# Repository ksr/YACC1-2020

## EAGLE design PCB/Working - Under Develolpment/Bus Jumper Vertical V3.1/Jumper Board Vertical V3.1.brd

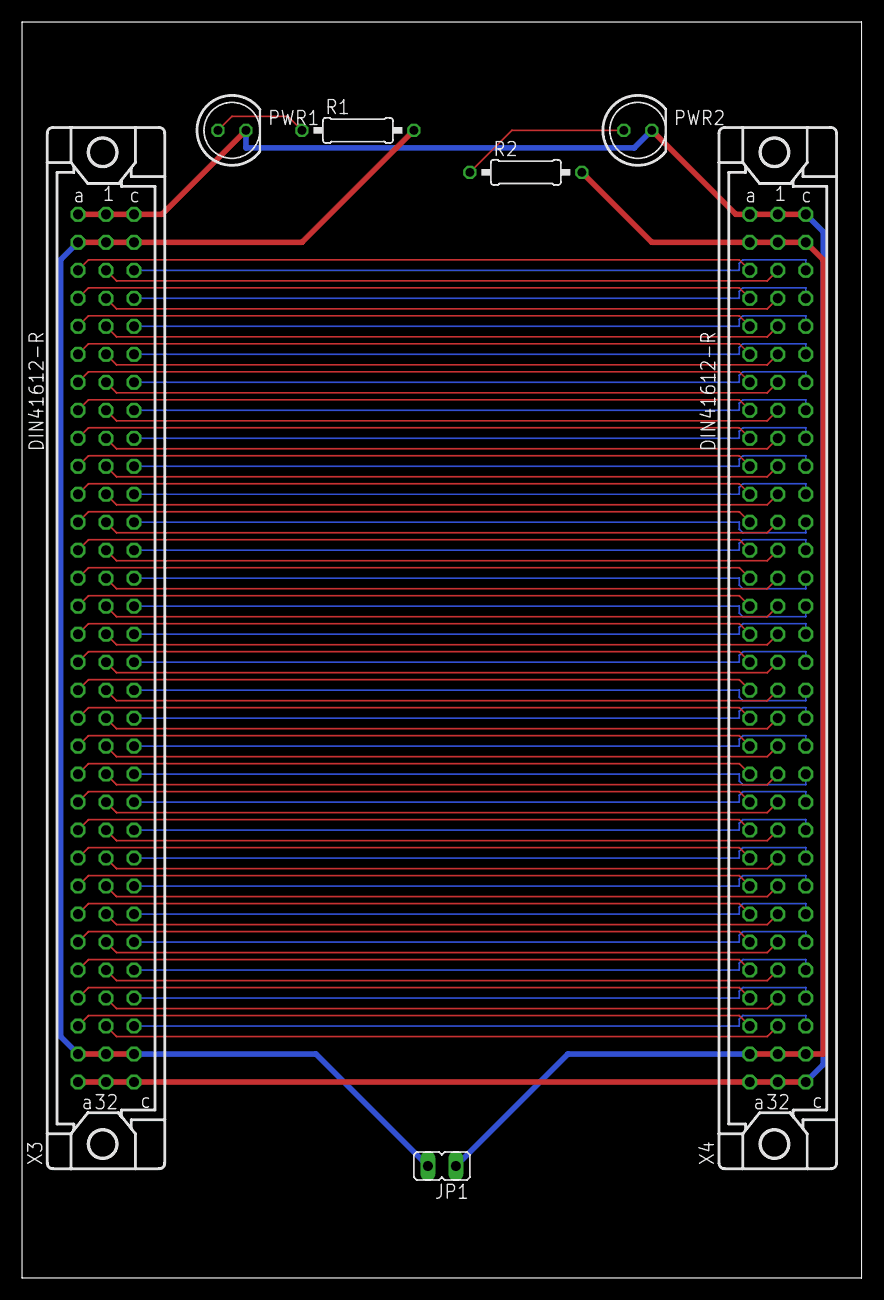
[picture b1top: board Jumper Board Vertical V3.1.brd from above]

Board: 2 copper layers, 76.2 x 114.0 mm, 7 parts (0 on the bottom side), 89 nets.

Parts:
JP1: JP1
PWR1, PWR2: LED5MM
R1, R2: 330; 0207/10
X3, X4: MABC96R

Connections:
GND: PWR1.K, PWR2.K, X3.A1, X3.A32, X3.B1, X3.B32, X3.C1, X3.C32, X4.A1, X4.A32, X4.B1, X4.B32, X4.C1, X4.C32
unnamed: X3.A3, X4.A3
unnamed: X3.A4, X4.A4
unnamed: X3.A5, X4.A5
unnamed: X3.A6, X4.A6
unnamed: X3.A7, X4.A7
unnamed: X3.A8, X4.A8
unnamed: X3.A9, X4.A9
unnamed: X3.A10, X4.A10
unnamed: X3.A11, X4.A11
unnamed: X3.A12, X4.A12
unnamed: X3.A13, X4.A13
unnamed: X3.A14, X4.A14
unnamed: X3.A15, X4.A15
unnamed: X3.A16, X4.A16
unnamed: X3.A17, X4.A17
unnamed: X3.A18, X4.A18
unnamed: X3.A19, X4.A19
unnamed: X3.A20, X4.A20
unnamed: X3.A21, X4.A21
unnamed: X3.A22, X4.A22
unnamed: X3.A23, X4.A23
unnamed: X3.A24, X4.A24
unnamed: X3.A25, X4.A25
unnamed: X3.A26, X4.A26
unnamed: X3.A27, X4.A27
unnamed: X3.A28, X4.A28
unnamed: X3.A29, X4.A29
unnamed: X3.A30, X4.A30
unnamed: PWR1.A, R1.1
unnamed: PWR2.A, R2.1
unnamed: X3.B3, X4.B3
unnamed: X3.B4, X4.B4
unnamed: X3.B5, X4.B5
unnamed: X3.B6, X4.B6
unnamed: X3.B7, X4.B7
unnamed: X3.B8, X4.B8
unnamed: X3.B9, X4.B9
unnamed: X3.B10, X4.B10
unnamed: X3.B11, X4.B11
unnamed: X3.B12, X4.B12
unnamed: X3.B13, X4.B13
unnamed: X3.B14, X4.B14
unnamed: X3.B15, X4.B15
unnamed: X3.B16, X4.B16
unnamed: X3.B17, X4.B17
unnamed: X3.B18, X4.B18
unnamed: X3.B19, X4.B19
unnamed: X3.B20, X4.B20
unnamed: X3.B21, X4.B21
unnamed: X3.B22, X4.B22
unnamed: X3.B23, X4.B23
unnamed: X3.B24, X4.B24
unnamed: X3.B25, X4.B25
unnamed: X3.B26, X4.B26
unnamed: X3.B27, X4.B27
unnamed: X3.B28, X4.B28
unnamed: X3.B29, X4.B29
unnamed: X3.B30, X4.B30
unnamed: X3.C3, X4.C3
unnamed: X3.C4, X4.C4
unnamed: X3.C5, X4.C5
unnamed: X3.C6, X4.C6
unnamed: X3.C7, X4.C7
unnamed: X3.C8, X4.C8
unnamed: X3.C9, X4.C9
unnamed: X3.C10, X4.C10
unnamed: X3.C11, X4.C11
unnamed: X3.C12, X4.C12
unnamed: X3.C13, X4.C13
unnamed: X3.C14, X4.C14
unnamed: X3.C15, X4.C15
unnamed: X3.C16, X4.C16
unnamed: X3.C17, X4.C17
unnamed: X3.C18, X4.C18
unnamed: X3.C19, X4.C19
unnamed: X3.C20, X4.C20
unnamed: X3.C21, X4.C21
unnamed: X3.C22, X4.C22
unnamed: X3.C23, X4.C23
unnamed: X3.C24, X4.C24
unnamed: X3.C25, X4.C25
unnamed: X3.C26, X4.C26
unnamed: X3.C27, X4.C27
unnamed: X3.C28, X4.C28
unnamed: X3.C29, X4.C29
unnamed: X3.C30, X4.C30
V1: JP1.2, R1.2, X3.A2, X3.A31, X3.B2, X3.B31, X3.C2, X3.C31
V2: JP1.1, R2.2, X4.A2, X4.A31, X4.B2, X4.B31, X4.C2, X4.C31

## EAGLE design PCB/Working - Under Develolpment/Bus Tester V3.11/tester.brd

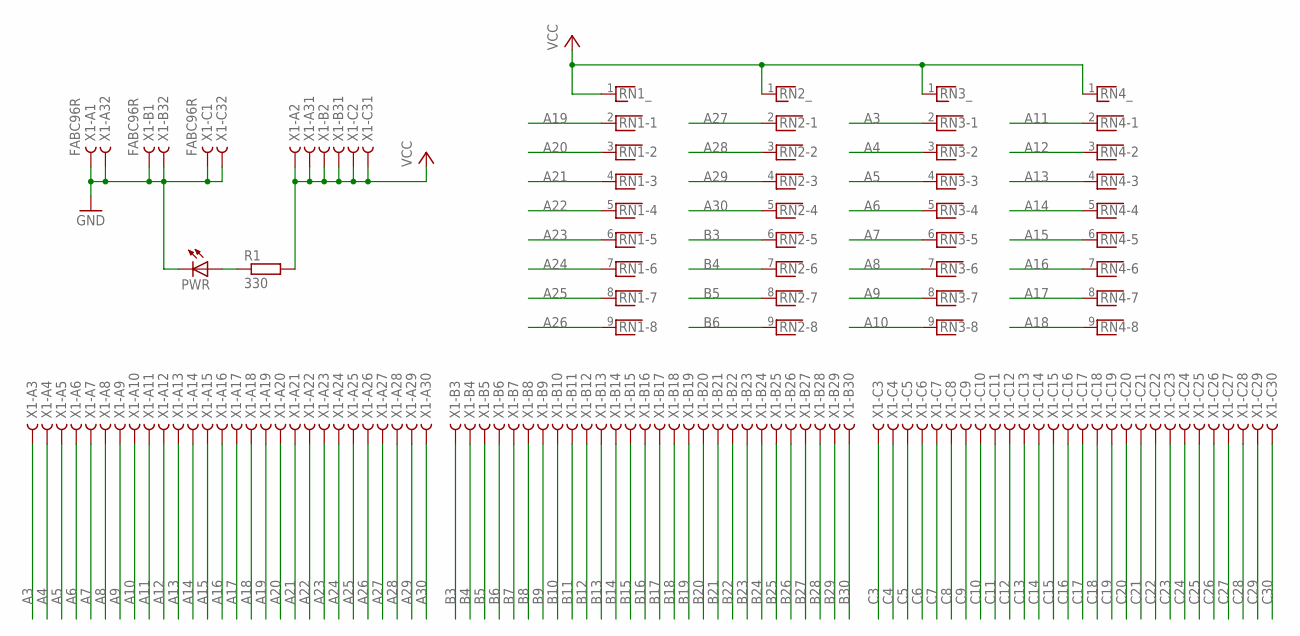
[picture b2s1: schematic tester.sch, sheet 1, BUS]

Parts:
PWR: LED5MM
R1: 330; 0207/10
RN1, RN2, RN3, RN4: RNX8; RN-9
X1: FABC96R

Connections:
A3: RN3.2, X1.A3; also elsewhere on the board
A4: RN3.3, X1.A4; also elsewhere on the board
A5: RN3.4, X1.A5; also elsewhere on the board
A6: RN3.5, X1.A6; also elsewhere on the board
A7: RN3.6, X1.A7; also elsewhere on the board
A8: RN3.7, X1.A8; also elsewhere on the board
A9: RN3.8, X1.A9; also elsewhere on the board
A10: RN3.9, X1.A10; also elsewhere on the board
A11: RN4.2, X1.A11; also elsewhere on the board
A12: RN4.3, X1.A12; also elsewhere on the board
A13: RN4.4, X1.A13; also elsewhere on the board
A14: RN4.5, X1.A14; also elsewhere on the board
A15: RN4.6, X1.A15; also elsewhere on the board
A16: RN4.7, X1.A16; also elsewhere on the board
A17: RN4.8, X1.A17; also elsewhere on the board
A18: RN4.9, X1.A18; also elsewhere on the board
A19: RN1.2, X1.A19; also elsewhere on the board
A20: RN1.3, X1.A20; also elsewhere on the board
A21: RN1.4, X1.A21; also elsewhere on the board
A22: RN1.5, X1.A22; also elsewhere on the board
A23: RN1.6, X1.A23; also elsewhere on the board
A24: RN1.7, X1.A24; also elsewhere on the board
A25: RN1.8, X1.A25; also elsewhere on the board
A26: RN1.9, X1.A26; also elsewhere on the board
A27: RN2.2, X1.A27; also elsewhere on the board
A28: RN2.3, X1.A28; also elsewhere on the board
A29: RN2.4, X1.A29; also elsewhere on the board
A30: RN2.5, X1.A30; also elsewhere on the board
B3: RN2.6, X1.B3; also elsewhere on the board
B4: RN2.7, X1.B4; also elsewhere on the board
B5: RN2.8, X1.B5; also elsewhere on the board
B6: RN2.9, X1.B6; also elsewhere on the board
B7: X1.B7; also elsewhere on the board
B8: X1.B8; also elsewhere on the board
B9: X1.B9; also elsewhere on the board
B10: X1.B10; also elsewhere on the board
B11: X1.B11; also elsewhere on the board
B12: X1.B12; also elsewhere on the board
B13: X1.B13; also elsewhere on the board
B14: X1.B14; also elsewhere on the board
B15: X1.B15; also elsewhere on the board
B16: X1.B16; also elsewhere on the board
B17: X1.B17; also elsewhere on the board
B18: X1.B18; also elsewhere on the board
B19: X1.B19; also elsewhere on the board
B20: X1.B20; also elsewhere on the board
B21: X1.B21; also elsewhere on the board
B22: X1.B22; also elsewhere on the board
B23: X1.B23; also elsewhere on the board
B24: X1.B24; also elsewhere on the board
B25: X1.B25; also elsewhere on the board
B26: X1.B26; also elsewhere on the board
B27: X1.B27; also elsewhere on the board
B28: X1.B28; also elsewhere on the board
B29: X1.B29; also elsewhere on the board
B30: X1.B30; also elsewhere on the board
C3: X1.C3; also elsewhere on the board
C4: X1.C4; also elsewhere on the board
C5: X1.C5; also elsewhere on the board
C6: X1.C6; also elsewhere on the board
C7: X1.C7; also elsewhere on the board
C8: X1.C8; also elsewhere on the board
C9: X1.C9; also elsewhere on the board
C10: X1.C10; also elsewhere on the board
C11: X1.C11; also elsewhere on the board
C12: X1.C12; also elsewhere on the board
C13: X1.C13; also elsewhere on the board
C14: X1.C14; also elsewhere on the board
C15: X1.C15; also elsewhere on the board
C16: X1.C16; also elsewhere on the board
C17: X1.C17; also elsewhere on the board
C18: X1.C18; also elsewhere on the board
C19: X1.C19; also elsewhere on the board
C20: X1.C20; also elsewhere on the board
C21: X1.C21; also elsewhere on the board
C22: X1.C22; also elsewhere on the board
C23: X1.C23; also elsewhere on the board
C24: X1.C24; also elsewhere on the board
C25: X1.C25; also elsewhere on the board
C26: X1.C26; also elsewhere on the board
C27: X1.C27; also elsewhere on the board
C28: X1.C28; also elsewhere on the board
C29: X1.C29; also elsewhere on the board
C30: X1.C30; also elsewhere on the board
GND: PWR.K (C), X1.A1, X1.A32, X1.B1, X1.B32, X1.C1, X1.C32; also elsewhere on the board
unnamed: PWR.A, R1.1
VCC: R1.2, RN1.1, RN2.1, RN3.1, RN4.1, X1.A2, X1.A31, X1.B2, X1.B31, X1.C2, X1.C31; also elsewhere on the board

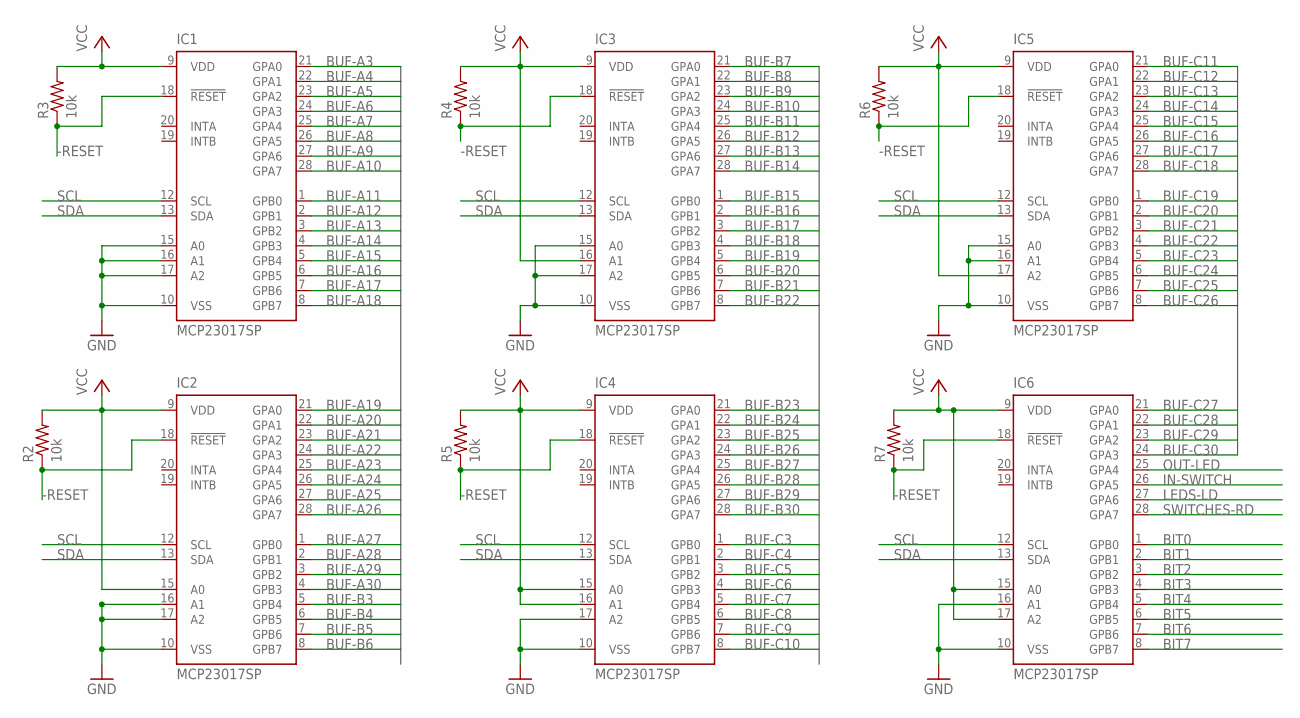
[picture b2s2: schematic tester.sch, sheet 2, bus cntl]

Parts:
IC1, IC2, IC3, IC4, IC5, IC6: MCP23017SP; DIL28-3
R2, R3, R4, R5, R6, R7: 10k; 0207/10

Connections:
-RESET: IC1.18 (!RESET), IC2.18 (!RESET), IC3.18 (!RESET), IC4.18 (!RESET), IC5.18 (!RESET), IC6.18 (!RESET), R2.1, R3.1, R4.1, R5.1, R6.1, R7.1; also elsewhere on the board
BIT0: IC6.1 (GPB0); also elsewhere on the board
BIT1: IC6.2 (GPB1); also elsewhere on the board
BIT2: IC6.3 (GPB2); also elsewhere on the board
BIT3: IC6.4 (GPB3); also elsewhere on the board
BIT4: IC6.5 (GPB4); also elsewhere on the board
BIT5: IC6.6 (GPB5); also elsewhere on the board
BIT6: IC6.7 (GPB6); also elsewhere on the board
BIT7: IC6.8 (GPB7); also elsewhere on the board
BUF-A3: IC1.21 (GPA0); also elsewhere on the board
BUF-A4: IC1.22 (GPA1); also elsewhere on the board
BUF-A5: IC1.23 (GPA2); also elsewhere on the board
BUF-A6: IC1.24 (GPA3); also elsewhere on the board
BUF-A7: IC1.25 (GPA4); also elsewhere on the board
BUF-A8: IC1.26 (GPA5); also elsewhere on the board
BUF-A9: IC1.27 (GPA6); also elsewhere on the board
BUF-A10: IC1.28 (GPA7); also elsewhere on the board
BUF-A11: IC1.1 (GPB0); also elsewhere on the board
BUF-A12: IC1.2 (GPB1); also elsewhere on the board
BUF-A13: IC1.3 (GPB2); also elsewhere on the board
BUF-A14: IC1.4 (GPB3); also elsewhere on the board
BUF-A15: IC1.5 (GPB4); also elsewhere on the board
BUF-A16: IC1.6 (GPB5); also elsewhere on the board
BUF-A17: IC1.7 (GPB6); also elsewhere on the board
BUF-A18: IC1.8 (GPB7); also elsewhere on the board
BUF-A19: IC2.21 (GPA0); also elsewhere on the board
BUF-A20: IC2.22 (GPA1); also elsewhere on the board
BUF-A21: IC2.23 (GPA2); also elsewhere on the board
BUF-A22: IC2.24 (GPA3); also elsewhere on the board
BUF-A23: IC2.25 (GPA4); also elsewhere on the board
BUF-A24: IC2.26 (GPA5); also elsewhere on the board
BUF-A25: IC2.27 (GPA6); also elsewhere on the board
BUF-A26: IC2.28 (GPA7); also elsewhere on the board
BUF-A27: IC2.1 (GPB0); also elsewhere on the board
BUF-A28: IC2.2 (GPB1); also elsewhere on the board
BUF-A29: IC2.3 (GPB2); also elsewhere on the board
BUF-A30: IC2.4 (GPB3); also elsewhere on the board
BUF-B3: IC2.5 (GPB4); also elsewhere on the board
BUF-B4: IC2.6 (GPB5); also elsewhere on the board
BUF-B5: IC2.7 (GPB6); also elsewhere on the board
BUF-B6: IC2.8 (GPB7); also elsewhere on the board
BUF-B7: IC3.21 (GPA0); also elsewhere on the board
BUF-B8: IC3.22 (GPA1); also elsewhere on the board
BUF-B9: IC3.23 (GPA2); also elsewhere on the board
BUF-B10: IC3.24 (GPA3); also elsewhere on the board
BUF-B11: IC3.25 (GPA4); also elsewhere on the board
BUF-B12: IC3.26 (GPA5); also elsewhere on the board
BUF-B13: IC3.27 (GPA6); also elsewhere on the board
BUF-B14: IC3.28 (GPA7); also elsewhere on the board
BUF-B15: IC3.1 (GPB0); also elsewhere on the board
BUF-B16: IC3.2 (GPB1); also elsewhere on the board
BUF-B17: IC3.3 (GPB2); also elsewhere on the board
BUF-B18: IC3.4 (GPB3); also elsewhere on the board
BUF-B19: IC3.5 (GPB4); also elsewhere on the board
BUF-B20: IC3.6 (GPB5); also elsewhere on the board
BUF-B21: IC3.7 (GPB6); also elsewhere on the board
BUF-B22: IC3.8 (GPB7); also elsewhere on the board
BUF-B23: IC4.21 (GPA0); also elsewhere on the board
BUF-B24: IC4.22 (GPA1); also elsewhere on the board
BUF-B25: IC4.23 (GPA2); also elsewhere on the board
BUF-B26: IC4.24 (GPA3); also elsewhere on the board
BUF-B27: IC4.25 (GPA4); also elsewhere on the board
BUF-B28: IC4.26 (GPA5); also elsewhere on the board
BUF-B29: IC4.27 (GPA6); also elsewhere on the board
BUF-B30: IC4.28 (GPA7); also elsewhere on the board
BUF-C3: IC4.1 (GPB0); also elsewhere on the board
BUF-C4: IC4.2 (GPB1); also elsewhere on the board
BUF-C5: IC4.3 (GPB2); also elsewhere on the board
BUF-C6: IC4.4 (GPB3); also elsewhere on the board
BUF-C7: IC4.5 (GPB4); also elsewhere on the board
BUF-C8: IC4.6 (GPB5); also elsewhere on the board
BUF-C9: IC4.7 (GPB6); also elsewhere on the board
BUF-C10: IC4.8 (GPB7); also elsewhere on the board
BUF-C11: IC5.21 (GPA0); also elsewhere on the board
BUF-C12: IC5.22 (GPA1); also elsewhere on the board
BUF-C13: IC5.23 (GPA2); also elsewhere on the board
BUF-C14: IC5.24 (GPA3); also elsewhere on the board
BUF-C15: IC5.25 (GPA4); also elsewhere on the board
BUF-C16: IC5.26 (GPA5); also elsewhere on the board
BUF-C17: IC5.27 (GPA6); also elsewhere on the board
BUF-C18: IC5.28 (GPA7); also elsewhere on the board
BUF-C19: IC5.1 (GPB0); also elsewhere on the board
BUF-C20: IC5.2 (GPB1); also elsewhere on the board
BUF-C21: IC5.3 (GPB2); also elsewhere on the board
BUF-C22: IC5.4 (GPB3); also elsewhere on the board
BUF-C23: IC5.5 (GPB4); also elsewhere on the board
BUF-C24: IC5.6 (GPB5); also elsewhere on the board
BUF-C25: IC5.7 (GPB6); also elsewhere on the board
BUF-C26: IC5.8 (GPB7); also elsewhere on the board
BUF-C27: IC6.21 (GPA0); also elsewhere on the board
BUF-C28: IC6.22 (GPA1); also elsewhere on the board
BUF-C29: IC6.23 (GPA2); also elsewhere on the board
BUF-C30: IC6.24 (GPA3); also elsewhere on the board
GND: IC1.10 (VSS), IC1.15 (A0), IC1.16 (A1), IC1.17 (A2), IC2.10 (VSS), IC2.16 (A1), IC2.17 (A2), IC3.10 (VSS), IC3.15 (A0), IC3.17 (A2), IC4.10 (VSS), IC4.17 (A2), IC5.10 (VSS), IC5.15 (A0), IC5.16 (A1), IC6.10 (VSS), IC6.16 (A1); also elsewhere on the board
IN-SWITCH: IC6.26 (GPA5); also elsewhere on the board
LEDS-LD: IC6.27 (GPA6); also elsewhere on the board
OUT-LED: IC6.25 (GPA4); also elsewhere on the board
SCL: IC1.12 (SCL), IC2.12 (SCL), IC3.12 (SCL), IC4.12 (SCL), IC5.12 (SCL), IC6.12 (SCL); also elsewhere on the board
SDA: IC1.13 (SDA), IC2.13 (SDA), IC3.13 (SDA), IC4.13 (SDA), IC5.13 (SDA), IC6.13 (SDA); also elsewhere on the board
SWITCHES-RD: IC6.28 (GPA7); also elsewhere on the board
VCC: IC1.9 (VDD), IC2.9 (VDD), IC2.15 (A0), IC3.9 (VDD), IC3.16 (A1), IC4.9 (VDD), IC4.15 (A0), IC4.16 (A1), IC5.9 (VDD), IC5.17 (A2), IC6.9 (VDD), IC6.15 (A0), IC6.17 (A2), R2.2, R3.2, R4.2, R5.2, R6.2, R7.2; also elsewhere on the board

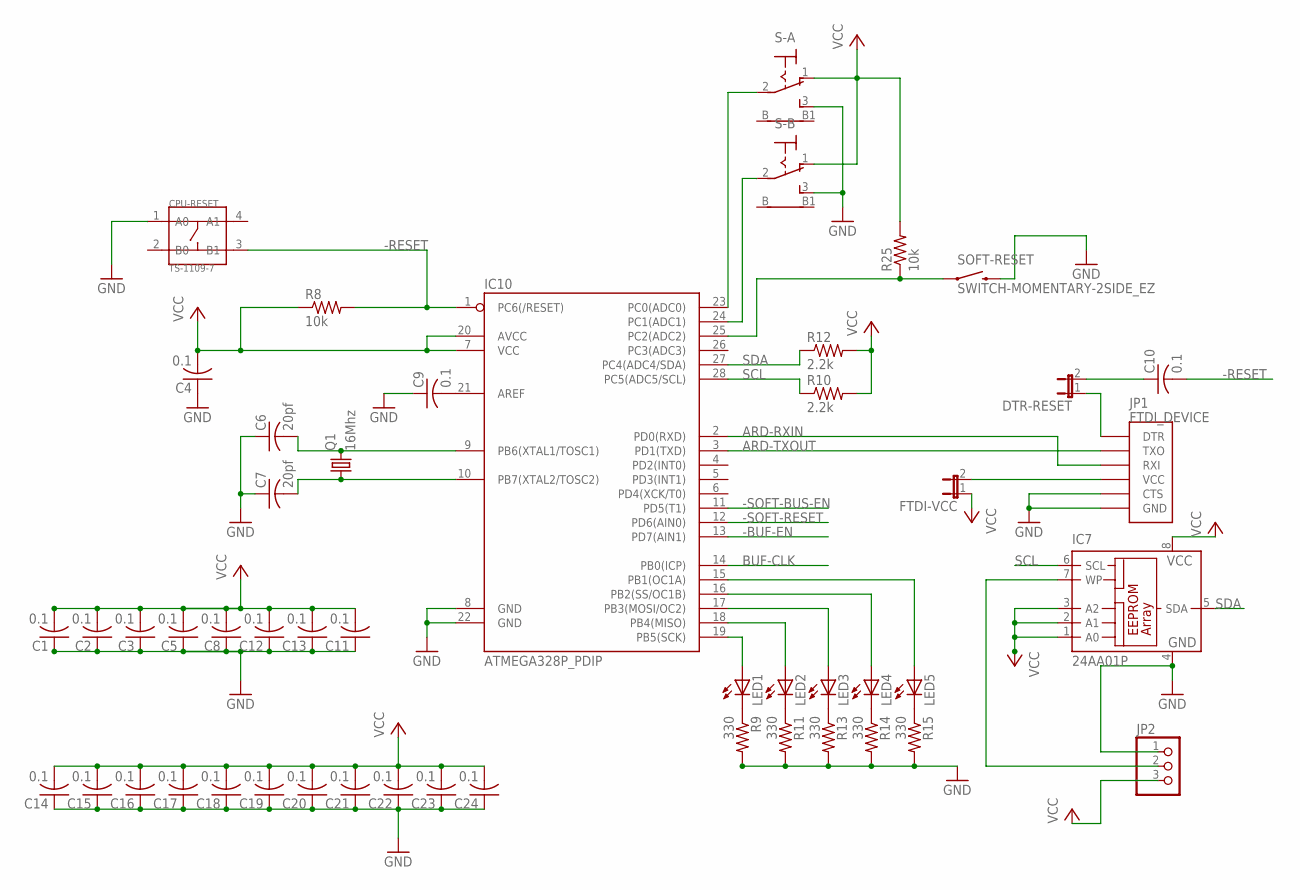
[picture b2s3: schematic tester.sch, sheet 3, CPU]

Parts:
C1, C2, C3, C4, C5, C8, C9, C10, C11, C12, C13, C14, C15, C16, C17, C18, C19, C20, C21, C22, C23, C24: 0.1; C025-024X044
C6, C7: 20pf; C025-024X044
CPU-RESET: TS-1109-7; SW4-6.2X6.2X5.0MM
DTR-RESET: JP1E; JP1
FTDI-VCC: JP1E; JP1
IC7: 24AA01P; DIL8
IC10: ATMEGA328P_PDIP; DIL28-3
JP1: FTDI_DEVICE; FTDI_DEVICE_SIDE
JP2: PINHD-1X3; 1X03
LED1, LED2, LED3, LED4, LED5: LED5MM
Q1: 16Mhz; HC49/S
R8, R25: 10k; 0207/10
R9, R11, R13, R14, R15: 330; 0207/10
R10, R12: 2.2k; 0207/10
S-A: 9070-1W
S-B: 9070-1W
SOFT-RESET: SWITCH-MOMENTARY-2SIDE_EZ; TACTILE-PTH-SIDEEZ

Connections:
-BUF-EN: IC10.13 (PD7(AIN1)); also elsewhere on the board
-RESET: C10.2, CPU-RESET.3 (B1), IC10.1 (PC6(/RESET)), R8.2; also elsewhere on the board
-SOFT-BUS-EN: IC10.11 (PD5(T1)); also elsewhere on the board
-SOFT-RESET: IC10.12 (PD6(AIN0)); also elsewhere on the board
ARD-RXIN: IC10.2 (PD0(RXD)), JP1.P$3 (RXI)
ARD-TXOUT: IC10.3 (PD1(TXD)), JP1.P$2 (TXO)
BUF-CLK: IC10.14 (PB0(ICP)); also elsewhere on the board
GND: C1.1, C2.1, C3.1, C4.1, C5.1, C6.1, C7.1, C8.1, C9.1, C11.1, C12.1, C13.1, C14.1, C15.1, C16.1, C17.1, C18.1, C19.1, C20.1, C21.1, C22.1, C23.1, C24.1, CPU-RESET.1 (A0), IC7.4 (GND), IC10.8 (GND), IC10.22 (GND), JP1.P$5 (CTS), JP1.P$6 (GND), JP2.1, R9.2, R11.2, R13.2, R14.2, R15.2, S-A.3 (S), S-B.3 (S), SOFT-RESET.2; also elsewhere on the board
unnamed: IC10.19 (PB5(SCK)), LED1.A
unnamed: IC7.7 (WP), JP2.2
unnamed: C6.2, IC10.9 (PB6(XTAL1/TOSC1)), Q1.2
unnamed: C7.2, IC10.10 (PB7(XTAL2/TOSC2)), Q1.1
unnamed: IC10.18 (PB4(MISO)), LED2.A
unnamed: IC10.17 (PB3(MOSI/OC2)), LED3.A
unnamed: IC10.16 (PB2(SS/OC1B)), LED4.A
unnamed: C10.1, DTR-RESET.2
unnamed: IC10.15 (PB1(OC1A)), LED5.A
unnamed: LED2.K (C), R11.1
unnamed: LED1.K (C), R9.1
unnamed: LED3.K (C), R13.1
unnamed: C9.2, IC10.21 (AREF)
unnamed: LED4.K (C), R14.1
unnamed: LED5.K (C), R15.1
unnamed: IC10.23 (PC0(ADC0)), S-A.2
unnamed: IC10.24 (PC1(ADC1)), S-B.2
unnamed: DTR-RESET.1, JP1.P$1 (DTR)
unnamed: FTDI-VCC.2, JP1.P$4 (VCC)
unnamed: IC10.25 (PC2(ADC2)), R25.1, SOFT-RESET.1
SCL: IC7.6 (SCL), IC10.28 (PC5(ADC5/SCL)), R10.1; also elsewhere on the board
SDA: IC7.5 (SDA), IC10.27 (PC4(ADC4/SDA)), R12.1; also elsewhere on the board
VCC: C1.2, C2.2, C3.2, C4.2, C5.2, C8.2, C11.2, C12.2, C13.2, C14.2, C15.2, C16.2, C17.2, C18.2, C19.2, C20.2, C21.2, C22.2, C23.2, C24.2, FTDI-VCC.1, IC7.1 (A0), IC7.2 (A1), IC7.3 (A2), IC7.8 (VCC), IC10.7 (VCC), IC10.20 (AVCC), JP2.3, R8.1, R10.2, R12.2, R25.2, S-A.1 (O), S-B.1 (O); also elsewhere on the board

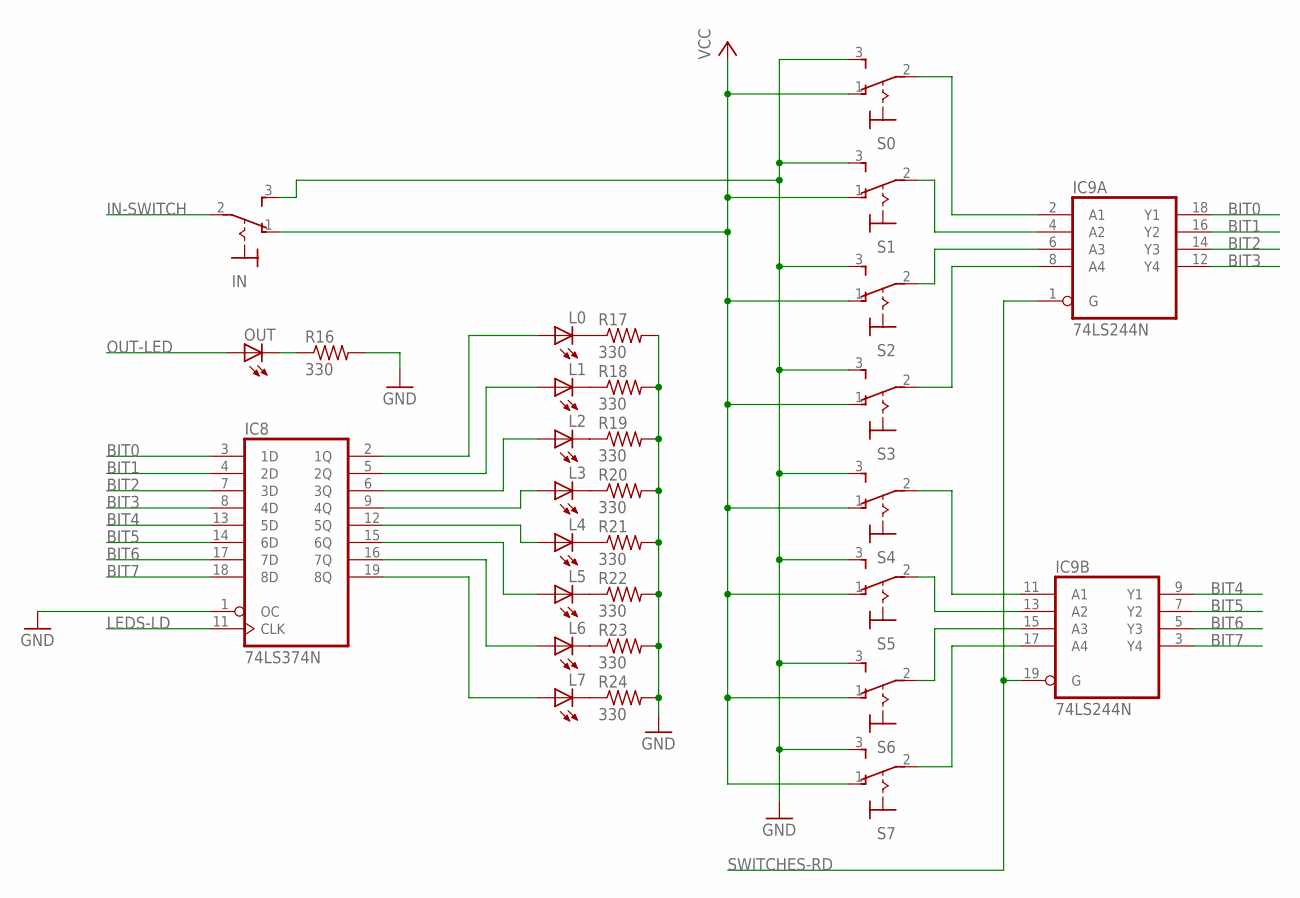
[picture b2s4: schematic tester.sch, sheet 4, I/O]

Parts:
IC8: 74LS374N; DIL20
IC9: 74LS244N; DIL20
IN: M9040P
L0, L1, L2, L3, L4, L5, L6, L7: LED5MM
OUT: LED5MM
R16, R17, R18, R19, R20, R21, R22, R23, R24: 330; 0207/10
S0, S1, S2, S3, S4, S5, S6, S7: M9040P

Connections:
BIT0: IC8.3 (1D), IC9.18 (Y1); also elsewhere on the board
BIT1: IC8.4 (2D), IC9.16 (Y2); also elsewhere on the board
BIT2: IC8.7 (3D), IC9.14 (Y3); also elsewhere on the board
BIT3: IC8.8 (4D), IC9.12 (Y4); also elsewhere on the board
BIT4: IC8.13 (5D), IC9.9 (Y1); also elsewhere on the board
BIT5: IC8.14 (6D), IC9.7 (Y2); also elsewhere on the board
BIT6: IC8.17 (7D), IC9.5 (Y3); also elsewhere on the board
BIT7: IC8.18 (8D), IC9.3 (Y4); also elsewhere on the board
GND: IC8.1 (OC), IC8.10 (GND), IC9.10 (GND), IN.3 (S), R16.2, R17.2, R18.2, R19.2, R20.2, R21.2, R22.2, R23.2, R24.2, S0.3 (S), S1.3 (S), S2.3 (S), S3.3 (S), S4.3 (S), S5.3 (S), S6.3 (S), S7.3 (S); also elsewhere on the board
IN-SWITCH: IN.2; also elsewhere on the board
LEDS-LD: IC8.11 (CLK); also elsewhere on the board
unnamed: L7.K (C), R24.1
unnamed: L6.K (C), R23.1
unnamed: L5.K (C), R22.1
unnamed: L4.K (C), R21.1
unnamed: L3.K (C), R20.1
unnamed: L2.K (C), R19.1
unnamed: L1.K (C), R18.1
unnamed: L0.K (C), R17.1
unnamed: OUT.K (C), R16.1
unnamed: IC8.5 (2Q), L1.A
unnamed: IC8.9 (4Q), L3.A
unnamed: IC8.12 (5Q), L4.A
unnamed: IC8.15 (6Q), L5.A
unnamed: IC8.6 (3Q), L2.A
unnamed: IC8.16 (7Q), L6.A
unnamed: IC8.19 (8Q), L7.A
unnamed: IC8.2 (1Q), L0.A
unnamed: IC9.2 (A1), S0.2
unnamed: IC9.8 (A4), S3.2
unnamed: IC9.6 (A3), S2.2
unnamed: IC9.4 (A2), S1.2
unnamed: IC9.11 (A1), S4.2
unnamed: IC9.17 (A4), S7.2
unnamed: IC9.13 (A2), S5.2
unnamed: IC9.15 (A3), S6.2
OUT-LED: OUT.A; also elsewhere on the board
SWITCHES-RD: IC9.1 (G), IC9.19 (G); also elsewhere on the board
VCC: IC8.20 (VCC), IC9.20 (VCC), IN.1 (O), S0.1 (O), S1.1 (O), S2.1 (O), S3.1 (O), S4.1 (O), S5.1 (O), S6.1 (O), S7.1 (O); also elsewhere on the board

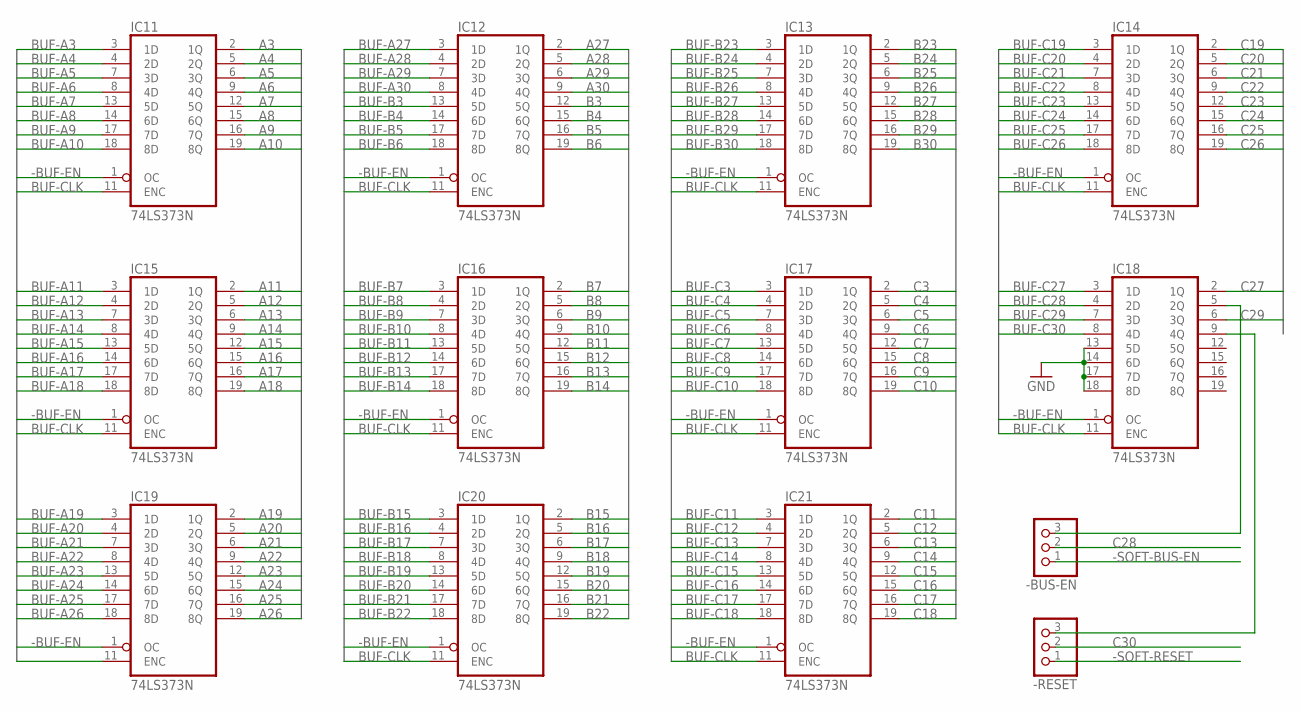
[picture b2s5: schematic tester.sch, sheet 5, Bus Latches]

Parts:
-BUS-EN: PINHD-1X3; 1X03
-RESET: PINHD-1X3; 1X03
IC11, IC12, IC13, IC14, IC15, IC16, IC17, IC18, IC19, IC20, IC21: 74LS373N; DIL20

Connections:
-BUF-EN: IC11.1 (OC), IC12.1 (OC), IC13.1 (OC), IC14.1 (OC), IC15.1 (OC), IC16.1 (OC), IC17.1 (OC), IC18.1 (OC), IC19.1 (OC), IC20.1 (OC), IC21.1 (OC); also elsewhere on the board
-SOFT-BUS-EN: -BUS-EN.1; also elsewhere on the board
-SOFT-RESET: -RESET.1; also elsewhere on the board
A3: IC11.2 (1Q); also elsewhere on the board
A4: IC11.5 (2Q); also elsewhere on the board
A5: IC11.6 (3Q); also elsewhere on the board
A6: IC11.9 (4Q); also elsewhere on the board
A7: IC11.12 (5Q); also elsewhere on the board
A8: IC11.15 (6Q); also elsewhere on the board
A9: IC11.16 (7Q); also elsewhere on the board
A10: IC11.19 (8Q); also elsewhere on the board
A11: IC15.2 (1Q); also elsewhere on the board
A12: IC15.5 (2Q); also elsewhere on the board
A13: IC15.6 (3Q); also elsewhere on the board
A14: IC15.9 (4Q); also elsewhere on the board
A15: IC15.12 (5Q); also elsewhere on the board
A16: IC15.15 (6Q); also elsewhere on the board
A17: IC15.16 (7Q); also elsewhere on the board
A18: IC15.19 (8Q); also elsewhere on the board
A19: IC19.2 (1Q); also elsewhere on the board
A20: IC19.5 (2Q); also elsewhere on the board
A21: IC19.6 (3Q); also elsewhere on the board
A22: IC19.9 (4Q); also elsewhere on the board
A23: IC19.12 (5Q); also elsewhere on the board
A24: IC19.15 (6Q); also elsewhere on the board
A25: IC19.16 (7Q); also elsewhere on the board
A26: IC19.19 (8Q); also elsewhere on the board
A27: IC12.2 (1Q); also elsewhere on the board
A28: IC12.5 (2Q); also elsewhere on the board
A29: IC12.6 (3Q); also elsewhere on the board
A30: IC12.9 (4Q); also elsewhere on the board
B3: IC12.12 (5Q); also elsewhere on the board
B4: IC12.15 (6Q); also elsewhere on the board
B5: IC12.16 (7Q); also elsewhere on the board
B6: IC12.19 (8Q); also elsewhere on the board
B7: IC16.2 (1Q); also elsewhere on the board
B8: IC16.5 (2Q); also elsewhere on the board
B9: IC16.6 (3Q); also elsewhere on the board
B10: IC16.9 (4Q); also elsewhere on the board
B11: IC16.12 (5Q); also elsewhere on the board
B12: IC16.15 (6Q); also elsewhere on the board
B13: IC16.16 (7Q); also elsewhere on the board
B14: IC16.19 (8Q); also elsewhere on the board
B15: IC20.2 (1Q); also elsewhere on the board
B16: IC20.5 (2Q); also elsewhere on the board
B17: IC20.6 (3Q); also elsewhere on the board
B18: IC20.9 (4Q); also elsewhere on the board
B19: IC20.12 (5Q); also elsewhere on the board
B20: IC20.15 (6Q); also elsewhere on the board
B21: IC20.16 (7Q); also elsewhere on the board
B22: IC20.19 (8Q); also elsewhere on the board
B23: IC13.2 (1Q); also elsewhere on the board
B24: IC13.5 (2Q); also elsewhere on the board
B25: IC13.6 (3Q); also elsewhere on the board
B26: IC13.9 (4Q); also elsewhere on the board
B27: IC13.12 (5Q); also elsewhere on the board
B28: IC13.15 (6Q); also elsewhere on the board
B29: IC13.16 (7Q); also elsewhere on the board
B30: IC13.19 (8Q); also elsewhere on the board
BUF-A3: IC11.3 (1D); also elsewhere on the board
BUF-A4: IC11.4 (2D); also elsewhere on the board
BUF-A5: IC11.7 (3D); also elsewhere on the board
BUF-A6: IC11.8 (4D); also elsewhere on the board
BUF-A7: IC11.13 (5D); also elsewhere on the board
BUF-A8: IC11.14 (6D); also elsewhere on the board
BUF-A9: IC11.17 (7D); also elsewhere on the board
BUF-A10: IC11.18 (8D); also elsewhere on the board
BUF-A11: IC15.3 (1D); also elsewhere on the board
BUF-A12: IC15.4 (2D); also elsewhere on the board
BUF-A13: IC15.7 (3D); also elsewhere on the board
BUF-A14: IC15.8 (4D); also elsewhere on the board
BUF-A15: IC15.13 (5D); also elsewhere on the board
BUF-A16: IC15.14 (6D); also elsewhere on the board
BUF-A17: IC15.17 (7D); also elsewhere on the board
BUF-A18: IC15.18 (8D); also elsewhere on the board
BUF-A19: IC19.3 (1D); also elsewhere on the board
BUF-A20: IC19.4 (2D); also elsewhere on the board
BUF-A21: IC19.7 (3D); also elsewhere on the board
BUF-A22: IC19.8 (4D); also elsewhere on the board
BUF-A23: IC19.13 (5D); also elsewhere on the board
BUF-A24: IC19.14 (6D); also elsewhere on the board
BUF-A25: IC19.17 (7D); also elsewhere on the board
BUF-A26: IC19.18 (8D); also elsewhere on the board
BUF-A27: IC12.3 (1D); also elsewhere on the board
BUF-A28: IC12.4 (2D); also elsewhere on the board
BUF-A29: IC12.7 (3D); also elsewhere on the board
BUF-A30: IC12.8 (4D); also elsewhere on the board
BUF-B3: IC12.13 (5D); also elsewhere on the board
BUF-B4: IC12.14 (6D); also elsewhere on the board
BUF-B5: IC12.17 (7D); also elsewhere on the board
BUF-B6: IC12.18 (8D); also elsewhere on the board
BUF-B7: IC16.3 (1D); also elsewhere on the board
BUF-B8: IC16.4 (2D); also elsewhere on the board
BUF-B9: IC16.7 (3D); also elsewhere on the board
BUF-B10: IC16.8 (4D); also elsewhere on the board
BUF-B11: IC16.13 (5D); also elsewhere on the board
BUF-B12: IC16.14 (6D); also elsewhere on the board
BUF-B13: IC16.17 (7D); also elsewhere on the board
BUF-B14: IC16.18 (8D); also elsewhere on the board
BUF-B15: IC20.3 (1D); also elsewhere on the board
BUF-B16: IC20.4 (2D); also elsewhere on the board
BUF-B17: IC20.7 (3D); also elsewhere on the board
BUF-B18: IC20.8 (4D); also elsewhere on the board
BUF-B19: IC20.13 (5D); also elsewhere on the board
BUF-B20: IC20.14 (6D); also elsewhere on the board
BUF-B21: IC20.17 (7D); also elsewhere on the board
BUF-B22: IC20.18 (8D); also elsewhere on the board
BUF-B23: IC13.3 (1D); also elsewhere on the board
BUF-B24: IC13.4 (2D); also elsewhere on the board
BUF-B25: IC13.7 (3D); also elsewhere on the board
BUF-B26: IC13.8 (4D); also elsewhere on the board
BUF-B27: IC13.13 (5D); also elsewhere on the board
BUF-B28: IC13.14 (6D); also elsewhere on the board
BUF-B29: IC13.17 (7D); also elsewhere on the board
BUF-B30: IC13.18 (8D); also elsewhere on the board
BUF-C3: IC17.3 (1D); also elsewhere on the board
BUF-C4: IC17.4 (2D); also elsewhere on the board
BUF-C5: IC17.7 (3D); also elsewhere on the board
BUF-C6: IC17.8 (4D); also elsewhere on the board
BUF-C7: IC17.13 (5D); also elsewhere on the board
BUF-C8: IC17.14 (6D); also elsewhere on the board
BUF-C9: IC17.17 (7D); also elsewhere on the board
BUF-C10: IC17.18 (8D); also elsewhere on the board
BUF-C11: IC21.3 (1D); also elsewhere on the board
BUF-C12: IC21.4 (2D); also elsewhere on the board
BUF-C13: IC21.7 (3D); also elsewhere on the board
BUF-C14: IC21.8 (4D); also elsewhere on the board
BUF-C15: IC21.13 (5D); also elsewhere on the board
BUF-C16: IC21.14 (6D); also elsewhere on the board
BUF-C17: IC21.17 (7D); also elsewhere on the board
BUF-C18: IC21.18 (8D); also elsewhere on the board
BUF-C19: IC14.3 (1D); also elsewhere on the board
BUF-C20: IC14.4 (2D); also elsewhere on the board
BUF-C21: IC14.7 (3D); also elsewhere on the board
BUF-C22: IC14.8 (4D); also elsewhere on the board
BUF-C23: IC14.13 (5D); also elsewhere on the board
BUF-C24: IC14.14 (6D); also elsewhere on the board
BUF-C25: IC14.17 (7D); also elsewhere on the board
BUF-C26: IC14.18 (8D); also elsewhere on the board
BUF-C27: IC18.3 (1D); also elsewhere on the board
BUF-C28: IC18.4 (2D); also elsewhere on the board
BUF-C29: IC18.7 (3D); also elsewhere on the board
BUF-C30: IC18.8 (4D); also elsewhere on the board
BUF-CLK: IC11.11 (ENC), IC12.11 (ENC), IC13.11 (ENC), IC14.11 (ENC), IC15.11 (ENC), IC16.11 (ENC), IC17.11 (ENC), IC18.11 (ENC), IC19.11 (ENC), IC20.11 (ENC), IC21.11 (ENC); also elsewhere on the board
C3: IC17.2 (1Q); also elsewhere on the board
C4: IC17.5 (2Q); also elsewhere on the board
C5: IC17.6 (3Q); also elsewhere on the board
C6: IC17.9 (4Q); also elsewhere on the board
C7: IC17.12 (5Q); also elsewhere on the board
C8: IC17.15 (6Q); also elsewhere on the board
C9: IC17.16 (7Q); also elsewhere on the board
C10: IC17.19 (8Q); also elsewhere on the board
C11: IC21.2 (1Q); also elsewhere on the board
C12: IC21.5 (2Q); also elsewhere on the board
C13: IC21.6 (3Q); also elsewhere on the board
C14: IC21.9 (4Q); also elsewhere on the board
C15: IC21.12 (5Q); also elsewhere on the board
C16: IC21.15 (6Q); also elsewhere on the board
C17: IC21.16 (7Q); also elsewhere on the board
C18: IC21.19 (8Q); also elsewhere on the board
C19: IC14.2 (1Q); also elsewhere on the board
C20: IC14.5 (2Q); also elsewhere on the board
C21: IC14.6 (3Q); also elsewhere on the board
C22: IC14.9 (4Q); also elsewhere on the board
C23: IC14.12 (5Q); also elsewhere on the board
C24: IC14.15 (6Q); also elsewhere on the board
C25: IC14.16 (7Q); also elsewhere on the board
C26: IC14.19 (8Q); also elsewhere on the board
C27: IC18.2 (1Q); also elsewhere on the board
C28: -BUS-EN.2; also elsewhere on the board
C29: IC18.6 (3Q); also elsewhere on the board
C30: -RESET.2; also elsewhere on the board
GND: IC11.10 (GND), IC12.10 (GND), IC13.10 (GND), IC14.10 (GND), IC15.10 (GND), IC16.10 (GND), IC17.10 (GND), IC18.10 (GND), IC18.13 (5D), IC18.14 (6D), IC18.17 (7D), IC18.18 (8D), IC19.10 (GND), IC20.10 (GND), IC21.10 (GND); also elsewhere on the board
unnamed: -BUS-EN.3, IC18.5 (2Q)
unnamed: -RESET.3, IC18.9 (4Q)
VCC: IC11.20 (VCC), IC12.20 (VCC), IC13.20 (VCC), IC14.20 (VCC), IC15.20 (VCC), IC16.20 (VCC), IC17.20 (VCC), IC18.20 (VCC), IC19.20 (VCC), IC20.20 (VCC), IC21.20 (VCC); also elsewhere on the board

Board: 4 copper layers, 110 parts (0 on the bottom side), 239 nets, no tracks yet.

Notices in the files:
parts and their libraries:
SparkFun-DigitalIC: Licensing: CC v3.0 Share-Alike You are welcome to use this library for commercial purposes.
SparkFun-Connectors: Licensing: Creative Commons ShareAlike 4.0 International - https://creativecommons.org/licenses/by-sa/4.0
